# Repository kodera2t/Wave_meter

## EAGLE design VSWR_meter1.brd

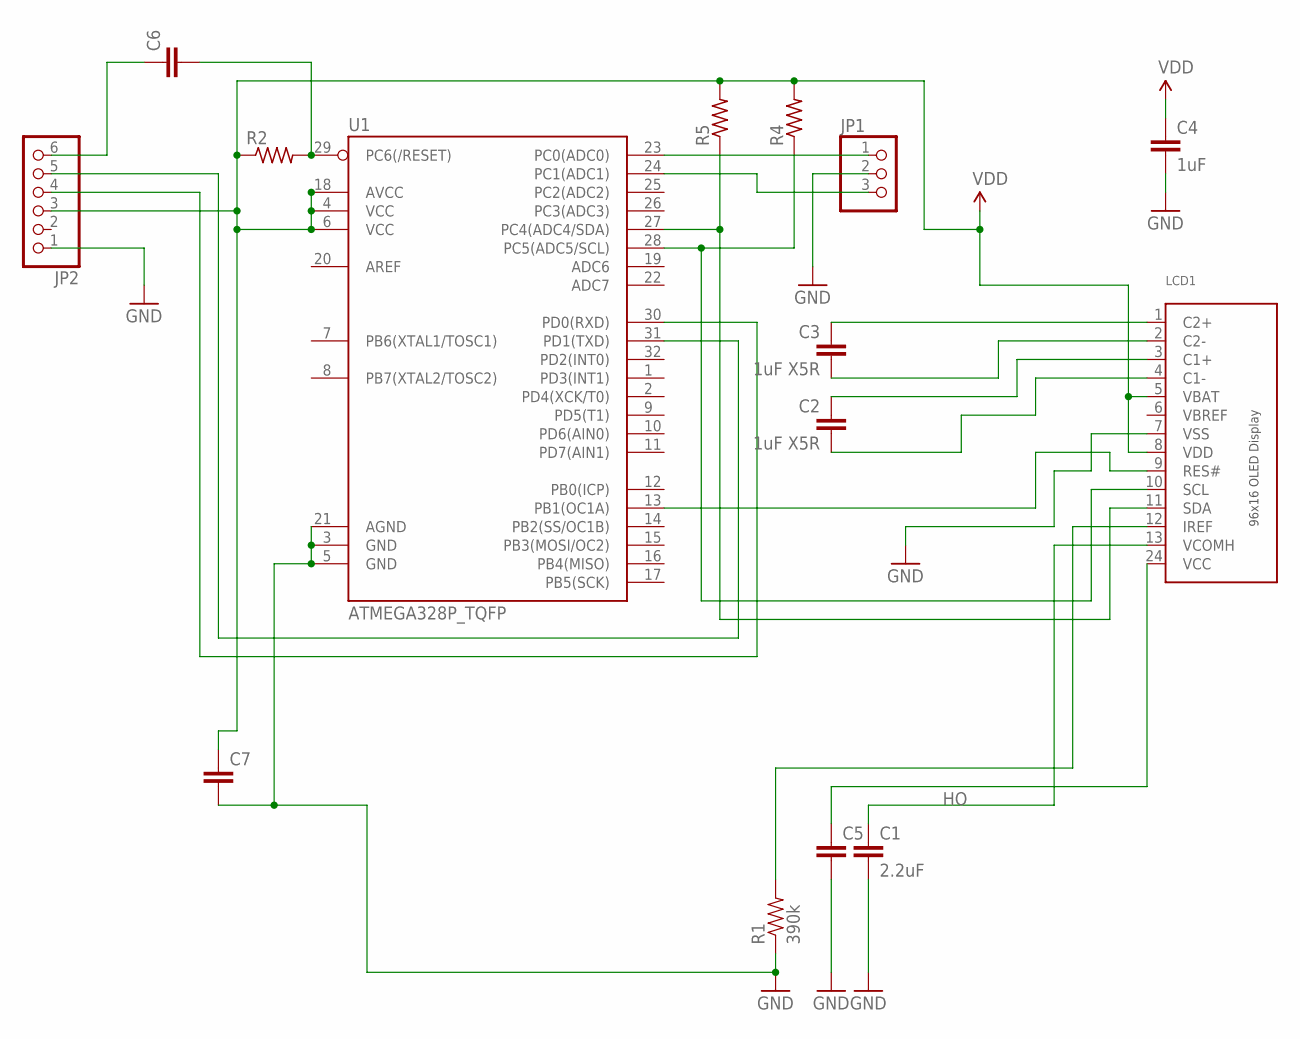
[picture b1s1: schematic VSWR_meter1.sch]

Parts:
C1: 2.2uF; 0805
C2, C3: 1uF X5R; 0805
C4: 1uF; 0603-CAP
C5, C6, C7: CC0603; C0603
JP1: HEADER-1X3; 1X03_OVAL
JP2: HEADER-1X6; 1X06_OVAL
LCD1: DISP_OLED_UG-9616GLBBG02; UG-9616GLBBG02_0.65MM_WRAPAROUND
R1: 390k; 0603-RES
R2, R4, R5: R-US_R0603; R0603
U1: ATMEGA328P_TQFP; TQFP32-08

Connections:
C1N: C2.2, LCD1.4 (C1-)
C1P: C2.1, LCD1.3 (C1+)
C2N: C3.2, LCD1.2 (C2-)
C2P: C3.1, LCD1.1 (C2+)
GND: C1.2, C4.2, C5.2, C7.2, JP1.2, JP2.1, LCD1.7 (VSS), R1.1, U1.3 (GND), U1.5 (GND), U1.21 (AGND)
HO: C1.1, LCD1.13 (VCOMH)
IREF: LCD1.12 (IREF), R1.2
unnamed: LCD1.11 (SDA), R5.1, U1.27 (PC4(ADC4/SDA))
unnamed: C6.2, R2.2, U1.29 (PC6(/RESET))
unnamed: LCD1.9 (RES#), U1.13 (PB1(OC1A))
unnamed: C6.1, JP2.6
unnamed: JP1.1, U1.23 (PC0(ADC0))
unnamed: LCD1.10 (SCL), R4.1, U1.28 (PC5(ADC5/SCL))
unnamed: JP1.3, U1.24 (PC1(ADC1))
unnamed: JP2.5, U1.31 (PD1(TXD))
unnamed: JP2.4, U1.30 (PD0(RXD))
VCOMH: C5.1, LCD1.24 (VCC)
VDD: C4.1, C7.1, JP2.3, LCD1.5 (VBAT), LCD1.8 (VDD), R2.1, R4.2, R5.2, U1.4 (VCC), U1.6 (VCC), U1.18 (AVCC)

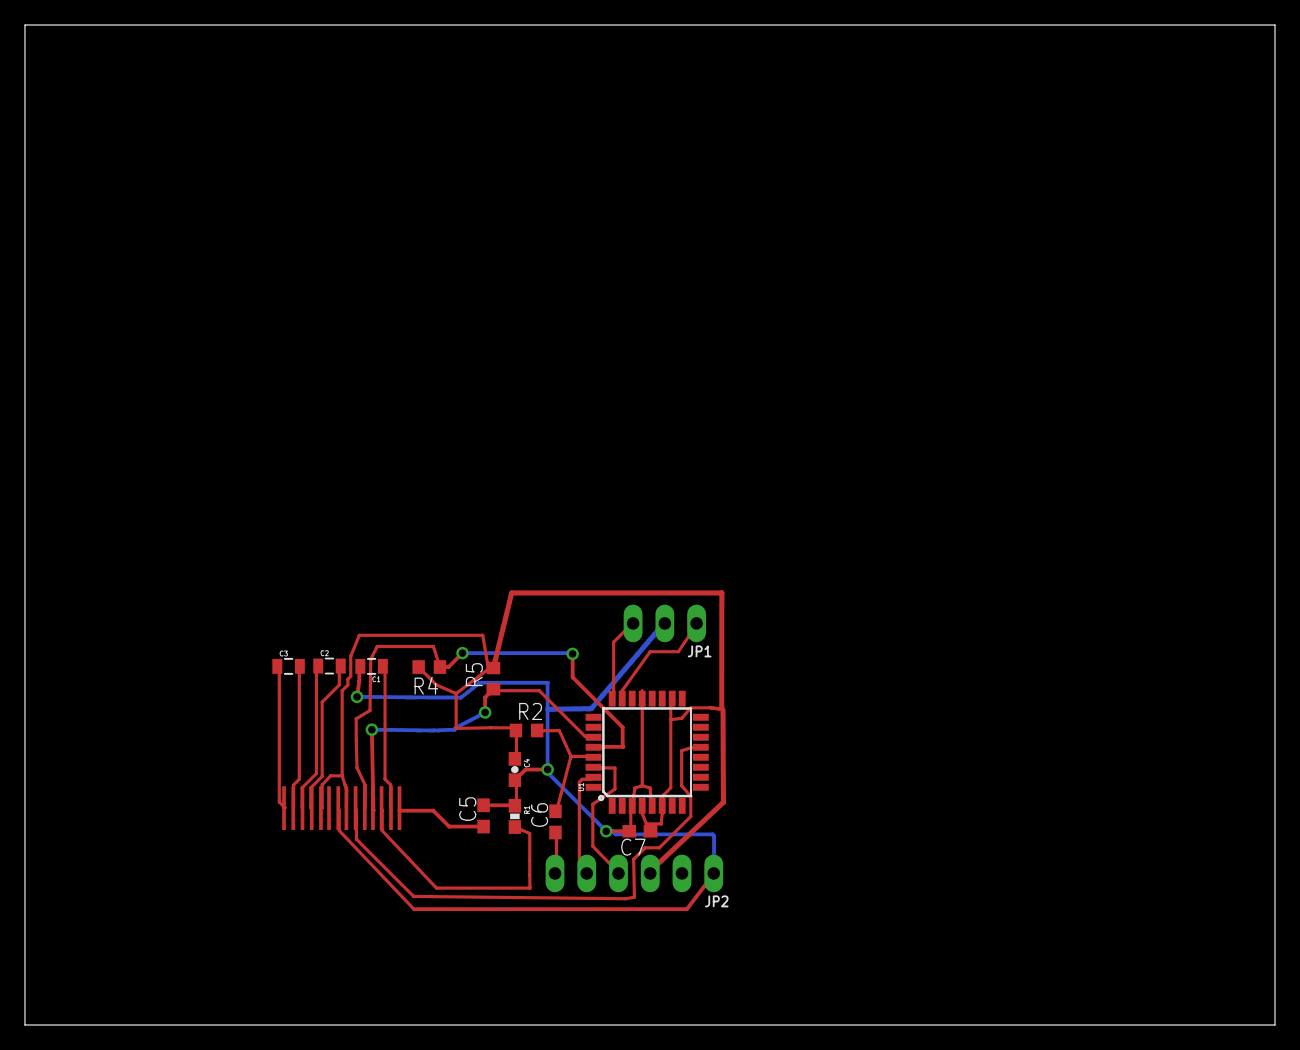
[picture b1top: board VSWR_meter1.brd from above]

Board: 2 copper layers, 100.0 x 80.0 mm, 15 parts (1 on the bottom side), 18 nets.

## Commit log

2015-10-18 Initial submission

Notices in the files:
parts and their libraries:
SparkFun-Passives: Licensing: Creative Commons ShareAlike 4.0 International - https://creativecommons.org/licenses/by-sa/4.0
OLED_mod: This work is placed in the public domain, and may be freely used for commercial and non-commercial work with the following conditions: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
